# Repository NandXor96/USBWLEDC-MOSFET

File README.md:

# USBWLEDC MOSFET
USB Sound Reactive WLED Controller with MOSFET

## Features

- USB-C for flashing and power (max. 3A)
- Small size
- Cheap components
- MOSFET as "Relay"
- ICS-43434 MEMS Microphone (optional)
- Solder Pads instead of Screw Terminal Blocks

## BOM

|Designator    |Part                                            |Quantity|Value                  |LCSC Part #| Mouser Part # |
|--------------|------------------------------------------------|--------|-----------------------|-----------|---------------|
|C1*, C2, C6   |0805 MLCC                                       |3       |100nF 50V              |C49678     ||
|C3, C5        |0805 MLCC                                       |2       |22uF 25V               |C45783     ||
|C4            |D8.0mm P3.50mm ELKO                             |1       |330uF 25V              |           ||
|C7            |0805 MLCC                                       |1       |10uF 25V               |C15850     ||
|C8            |0805 MLCC                                       |1       |1uF 50V                |C28323     ||
|D1            |Schottky Diode                                  |1       |SS14                   |C2480      ||
|J10           |USB-C Receptacle                                |1       |USB_C_Receptacle_USB2.0|C2988369   ||
|MK1*          |InvenSense_ICS-43434 MEMS Microphone            |1       |ICS-43434              |           |410-ICS-43434|
|Q1            |N-Channel MOSFET                                |1       |IRLML6244              |C143946    ||
|Q2            |P-Channel MOSFET                                |1       |IRF7410TRPBF           |C148144    ||
|R1*           |0805 Resistor                                   |1       |100k                   |C149504    ||
|R2, R4, R5, R6|0805 Resistor                                   |4       |10k                    |C17414     ||
|R3            |0805 Resistor                                   |1       |330R                   |C17630     ||
|R7, R8        |0805 Resistor                                   |2       |5.1k                   |C27834     ||
|SW1           |Tactile Switch 6x3.5mm                          |1       |SWITCH                 |C3726366   ||
|U1            |USB-UART IC CH340N                              |1       |CH340N                 |C2977777   ||
|U2            |3.3V LDO AMS1117-3.3                            |1       |AMS1117-3.3            |C6186      ||
|U3            |ESP32-WROOM-32 D or E                           |1       |ESP32-WROOM-32         |C701341    |356-ESP32WRM32E132PH|

\* You can build it without the microphone. Then you don't need R1, C1 and MK1.

## Assembly

To assemble the PCB, I recommend using a hot plate or soldering oven for the upper side, and hand-soldering for the ESP32 on the back.
**Preheat** the PCB before soldering anything by hand and use a **powerful soldering iron**!  

## Disclaimer

The circuit board provided on this GitHub repository is offered "as is," without any warranties or guarantees of any kind. By accessing and utilizing this circuit board, you acknowledge and agree that you do so at your own risk.

The creator and contributor of this repository, shall not be held responsible or liable for any damages, losses, or injuries that may occur as a result of building and / or using this circuit board. This includes but is not limited to any direct, indirect, consequential, or incidental damages.

Electricity is dangerous. Only attempt this project if you know what you're doing.

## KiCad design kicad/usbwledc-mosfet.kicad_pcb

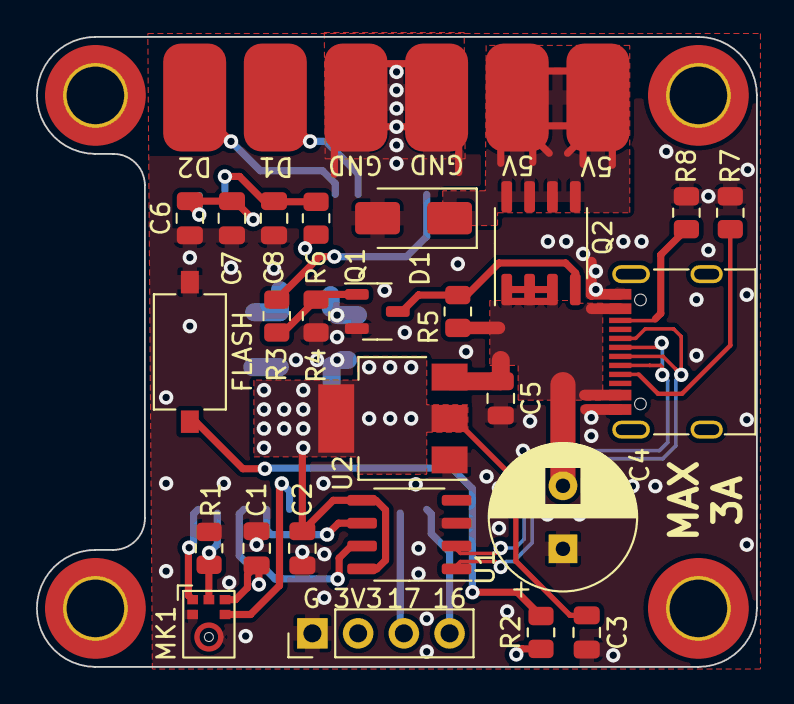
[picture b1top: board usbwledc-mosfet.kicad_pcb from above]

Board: 4 copper layers, 40.0 x 35.0 mm, 36 parts (1 on the bottom side), 22 nets.

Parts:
C1, C2, C6: 100nF; C_0805_2012Metric
C3, C5: 22uF; C_0805_2012Metric
C4: 330uF; CP_Radial_D8.0mm_P3.50mm
C7: 10uF; C_0805_2012Metric
C8: 1uF; C_0805_2012Metric
D1: SS14; D_SMA
H1, H2, H3, H4: MountingHole; MountingHole_3.2mm_M3_DIN965_Pad_TopBottom
J1, J4: 5V OUT PAD; SolderWirePad_1x01_SMD_3x6mm
J2: D1 PAD; SolderWirePad_1x01_SMD_3x6mm
J3, J6: GND PAD; SolderWirePad_1x01_SMD_3x6mm
J5: D2 PAD; SolderWirePad_1x01_SMD_3x6mm
J7: Conn_01x04_Pin; PinHeader_1x04_P2.54mm_Vertical
J10: USB_C_Receptacle_USB2.0; USB_C_Receptacle_G-Switch_GT-USB-7010ASV
MK1: ICS-43434; InvenSense_ICS-43434-6_3.5x2.65mm
Q1: IRLML6244; SOT-23-3
Q2: IRF7410TRPBF; SO-8_3.9x4.9mm_P1.27mm
R1: 100k; R_0805_2012Metric
R2, R4, R5, R6: 10k; R_0805_2012Metric
R3: 330R; R_0805_2012Metric
R7, R8: 5.1k; R_0805_2012Metric
SW1: FLASH_SW; SW_Tactile_SPST_NO_Straight_CK_PTS636Sx25SMTRLFS
U1: CH340N; SOP-8_3.9x4.9mm_P1.27mm
U2: AMS1117-3.3; SOT-223-3_TabPin2
U3: ESP32-WROOM-32

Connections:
+3V3: C1.1, C2.2, C3.1, C6.2, C7.1, J7.2, MK1.5 (VDD), R2.1, R6.1, U1.5 (VCC), U1.8 (V3), U2.2 (VO), U3.2 (VDD)
+5V: C4.2, C5.1, J10.A4 (VBUS), J10.A9 (VBUS), J10.B4 (VBUS), J10.B9 (VBUS), Q2.1 (S_1), Q2.2 (S_2), Q2.3 (S_3), R5.1, U2.3 (VI)
D+: J10.A6 (D+), J10.B6 (D+), U1.1 (UD+)
D-: J10.A7 (D-), J10.B7 (D-), U1.2 (UD-)
FLASH: R2.2, SW1.2, U3.25 (IO0)
GND: C1.2, C2.1, C3.2, C4.1, C5.2, C6.1, C7.2, C8.2, D1.2, J3.1, J6.1, J7.1, J10.A1 (GND), J10.A12 (GND), J10.B1 (GND), J10.B12 (GND), MK1.2 (LR), MK1.3 (GND), Q1.2 (S), R1.1, R4.2, R7.2, R8.2, SW1.1, U1.3 (GND), U2.1 (GND), U3.1 (GND), U3.15 (GND), U3.38 (GND), U3.39 (GND)
I2S_SCK: MK1.4 (SCK), U3.33 (IO21)
I2S_SD: MK1.6 (SD), R1.2, U3.36 (IO22)
I2S_WS: MK1.1 (WS), U3.37 (IO23)
IO16: J7.4, U3.27 (IO16)
IO17: J7.3, U3.28 (IO17)
unnamed: J10.A5 (CC1), R7.1
unnamed: J10.B5 (CC2), R8.1
unnamed: Q1.3 (D), Q2.4 (G), R5.2
unnamed: Q1.1 (G), R3.2, R4.1
unnamed: C8.1, R6.2, U3.3 (EN)
RELAY: R3.1, U3.12 (IO27)
RX: U1.6 (TXD), U3.34 (RXD0/IO3)
STRIP_5V: D1.1, J1.1, J4.1, Q2.5 (D_1), Q2.6 (D_2), Q2.7 (D_3), Q2.8 (D_4)
STRIP_DATA_1: J2.1, U3.9 (IO33)
STRIP_DATA_2: J5.1, U3.8 (IO32)
TX: U1.7 (RXD), U3.35 (TXD0/IO1)

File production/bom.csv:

Designator,Footprint,Quantity,Value,LCSC Part #
"C1, C2, C6",0805,3,100nF,C49678
"C3, C5",0805,2,22uF,C45783
C4,CP_Radial_D8.0mm_P3.50mm,1,330uF,
C7,0805,1,10uF,C15850 
C8,0805,1,1uF,C28323
D1,D_SMA,1,SS14,C2480
"H1, H2, H3, H4",MountingHole_3.2mm_M3_DIN965_Pad_TopBottom,4,MountingHole,
"J1, J4",SolderWirePad_1x01_SMD_3x6mm,2,5V OUT PAD,
J10,USB_C_Receptacle_G-Switch_GT-USB-7010ASV,1,USB_C_Receptacle_USB2.0,C2988369
J2,SolderWirePad_1x01_SMD_3x6mm,1,D1 PAD,
"J3, J6",SolderWirePad_1x01_SMD_3x6mm,2,GND PAD,
J5,SolderWirePad_1x01_SMD_3x6mm,1,D2 PAD,
J7,PinHeader_1x04_P2.54mm_Vertical,1,Conn_01x04_Pin,
MK1,InvenSense_ICS-43434-6_3.5x2.65mm,1,ICS-43434,
Q1,SOT-23-3,1,IRLML6244,C143946
Q2,SO-8_3.9x4.9mm_P1.27mm,1,IRF7410TRPBF,C148144
R1,0805,1,100k,C149504
"R2, R4, R5, R6",0805,4,10k,C17414
R3,0805,1,330R,C17630
"R7, R8",0805,2,5.1k,C27834
SW1,SW_Tactile_SPST_NO_Straight_CK_PTS636Sx25SMTRLFS,1,FLASH_SW,C3726366
U1,SOP-8_3.9x4.9mm_P1.27mm,1,CH340N,C2977777
U2,SOT-223-3_TabPin2,1,AMS1117-3.3,C6186
U3,ESP32-WROOM-32,1,ESP32-WROOM-32,C701341

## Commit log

2023-08-14 Corrected JLC-Text
